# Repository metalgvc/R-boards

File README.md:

#### Eagle libs, boards, schemes

##### mgvc.lbr
EAGLE lib contain following devices:
- GPS module GP4SF1109F2
- KL-5641-ASR LED
- MT3608
- CDRH74NP-220MC-B
- CN3085
- 40TPS12
- MICROSD-MR08
- SG5841

##### GP4SF1109F2-smd-to-dip
SMD to DIP adaptor for GP4SF1109F2 module

##### DC-DC-step-up-MT3608
DC/DC set-up converter board based on MT3608

##### DC-DC-sepic-MT3608
DC/DC SEPIC converter based on MT3608

##### GPS-module-board
GPS module GP4SF1109F2 board with bi-directional logic level converter 1.8 <-> 3.3/5... 
and linear stabilizator to 1.8v

##### Ni-MH-charger
Ni-MH charger module based on CN3085 
(module constructed without temperature monitoring)

##### tl494-pulse-generator
PWM on TL494 with mosfet

##### RF-detector

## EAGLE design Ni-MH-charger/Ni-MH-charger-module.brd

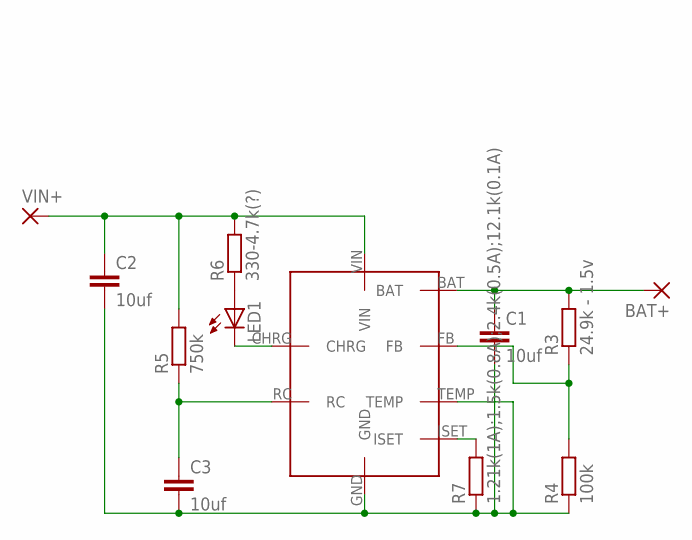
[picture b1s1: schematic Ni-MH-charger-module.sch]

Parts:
BAT+: SMD5; SMD2,54-5,08
C1, C2, C3: 10uf; C0805
LED1: LEDCHIPLED_0805; CHIPLED_0805
R3: 24.9k - 1.5v; R0805
R4: 100k; R0805
R5: 750k; R0805
R6: 330-4.7k(?); R0805
R7: 1.21k(1A);1.5k(0.8A);2.4k(0.5A);12.1k(0.1A); R0805
U$1: CN3085
VIN+: SMD5; SMD2,54-5,08

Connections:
BAT+: BAT+.1, C1.1, R3.2, U$1.BAT
GND: C1.2, C2.2, C3.2, R4.1, R7.1, U$1.GND, U$1.TEMP
unnamed: R3.1, R4.2, U$1.FB
unnamed: R7.2, U$1.ISET
unnamed: C3.1, R5.1, U$1.RC
unnamed: LED1.A, R6.1
unnamed: LED1.C, U$1.CHRG
VIN: C2.1, R5.2, R6.2, U$1.VIN, VIN+.1

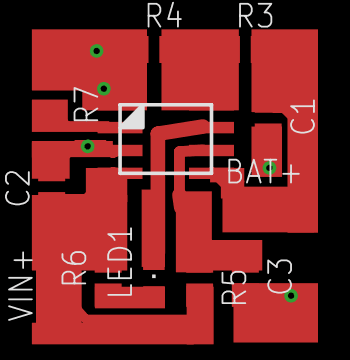
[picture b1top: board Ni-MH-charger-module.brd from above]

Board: 2 copper layers, 12 parts (0 on the bottom side), 8 nets.

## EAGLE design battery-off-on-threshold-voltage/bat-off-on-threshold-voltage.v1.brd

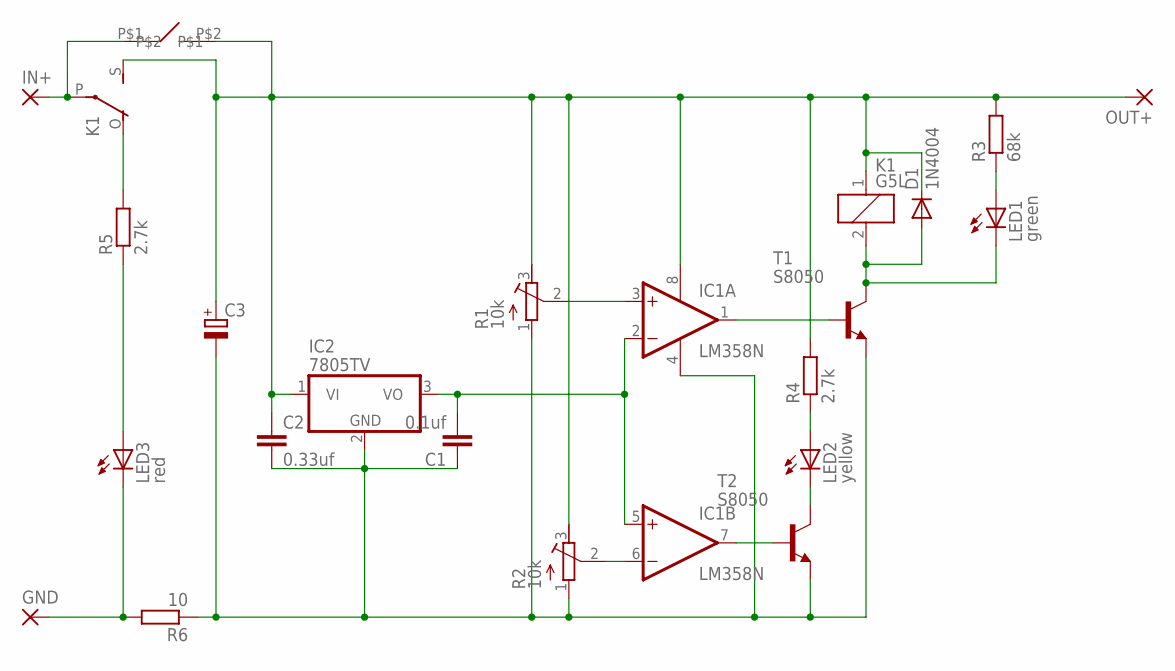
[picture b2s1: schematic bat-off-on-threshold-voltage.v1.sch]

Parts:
C1: 0.1uf; C050-025X075
C2: 0.33uf; C050-025X075
C3: CPOL-EUE2.5-6; E2,5-6
D1: 1N4004; DO41-10
GND: 3,81/1,1
IC1: LM358N; DIL08
IC2: 7805TV; TO220V
IN+: 3,81/1,1
K1: G5L; G5LE
LED1: green; LED3MM
LED2: yellow; LED3MM
LED3: red; LED3MM
OUT+: 3,81/1,1
R1, R2: 10k; RTRIM3296W
R3: 68k; 0204/7
R4, R5: 2.7k; 0204/7
R6: 10; 0204/7
T1, T2: S8050; TO92-EBC
U$1: BTN-6X6

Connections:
GND: C1.1, C2.2, C3.-, IC1.4 (V-), IC2.2 (GND), R1.1 (A), R2.1 (A), R6.1, T1.E, T2.E
unnamed: IC1.1 (OUT), T1.B
unnamed: IC1.7 (OUT), T2.B
unnamed: IC1.3 (+IN), R1.2 (S)
unnamed: IC1.6 (-IN), R2.2 (S)
unnamed: C2.1, C3.+, D1.C, IC1.8 (V+), IC2.1 (VI), K1.1, K1.S, OUT+.1, R1.3 (E), R2.3 (E), R3.2, R4.2, U$1.P$2
unnamed: C1.2, IC1.2 (-IN), IC1.5 (+IN), IC2.3 (VO)
unnamed: LED1.A, R3.1
unnamed: D1.A, K1.2, LED1.K (C), T1.C
unnamed: LED2.K (C), T2.C
unnamed: LED2.A, R4.1
unnamed: IN+.1, K1.P, U$1.P$1
unnamed: LED3.A, R5.1
unnamed: K1.O, R5.2
unnamed: GND.1, LED3.K (C), R6.2

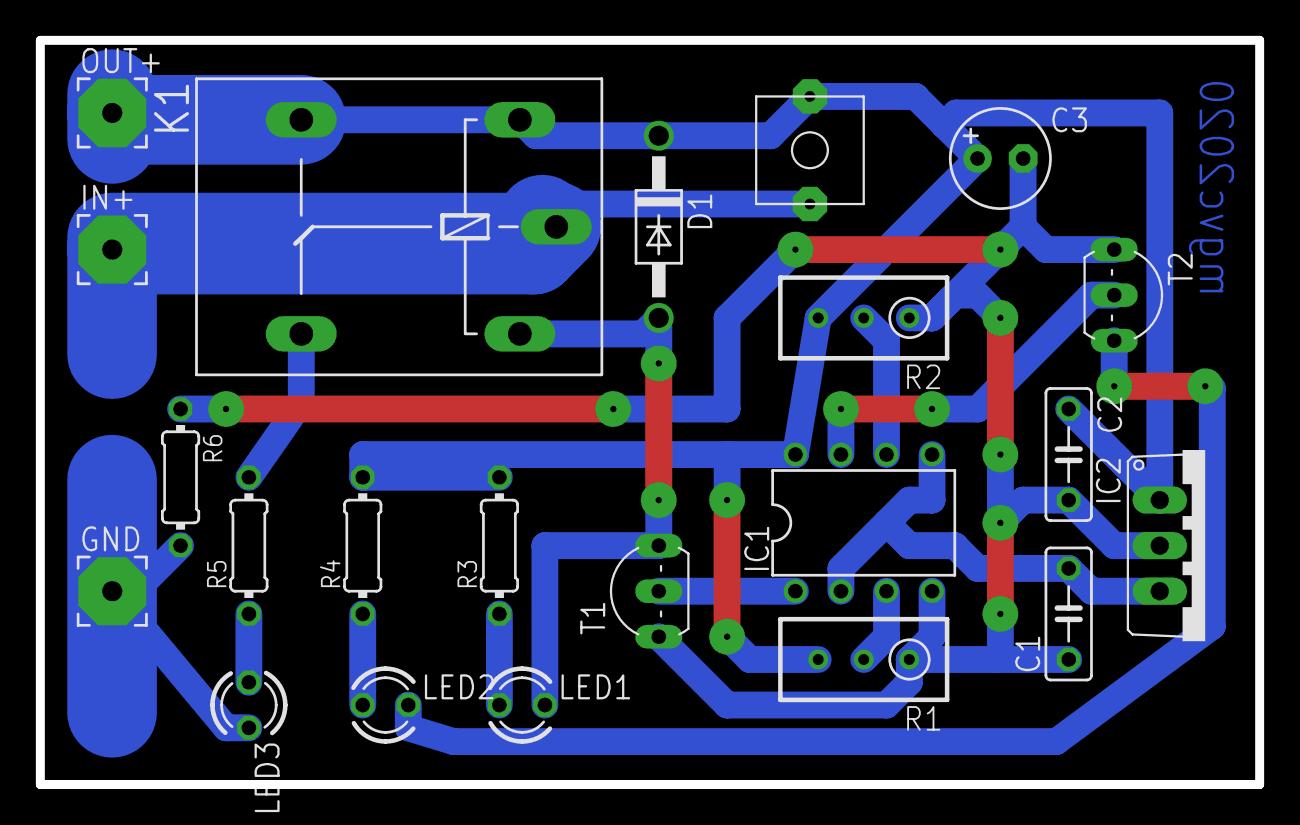
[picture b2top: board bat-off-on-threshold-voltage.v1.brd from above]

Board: 2 copper layers, 68.0 x 41.5 mm, 22 parts (0 on the bottom side), 15 nets.

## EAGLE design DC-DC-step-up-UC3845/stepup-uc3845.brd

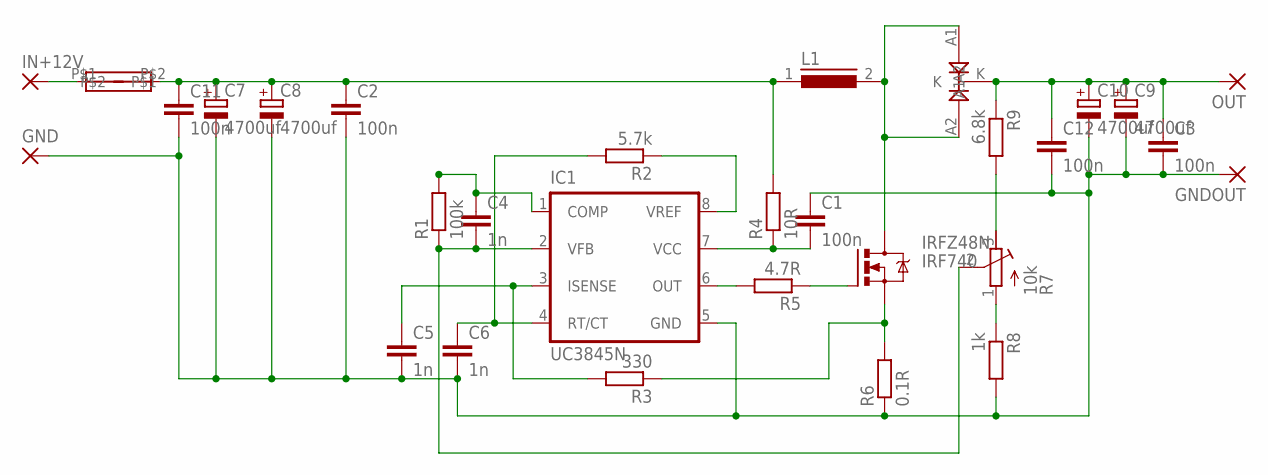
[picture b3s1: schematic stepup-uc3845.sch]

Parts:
C1, C2, C3, C11, C12: 100n; C050-025X075
C4, C5, C6: 1n; C050-025X075
C7, C8: 4700uf; E7,5-16
C9, C10: 4700uf; E7,5-18
F1: 10A; FUSE38X12
GND: 3,81/1,1
GNDOUT: 3,81/1,1
IC1: UC3845N; DIL08
IN+12V: 3,81/1,1
IRFZ48N: IRF740; TO220BV
L1: R3311D11; 11-33
OUT: 3,81/1,1
R1: 100k; 0204/7
R2: 5.7k; 0207/7
R3: 330; 0207/7
R4: 10R; 0617/17
R5: 4.7R; 0207/7
R6: 0.1R; 0922/22
R7: 10k; RTRIM3296W
R8: 1k; 0207/7
R9: 6.8k; 0207/7
U$1: TO-247-SHOTTKY-K; TO-247

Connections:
GND: C1.1, C2.2, C3.2, C5.2, C6.2, C7.-, C8.-, C9.-, C10.-, C11.2, C12.2, GND.1, GNDOUT.1, IC1.5 (GND), R6.1, R8.2
unnamed: C6.1, IC1.4 (RT/CT), R2.2
unnamed: C5.1, IC1.3 (ISENSE), R3.2
unnamed: C4.2, IC1.2 (VFB), R1.1, R7.2 (S)
unnamed: C4.1, IC1.1 (COMP), R1.2
unnamed: IC1.6 (OUT), R5.2
unnamed: IRFZ48N.G, R5.1
unnamed: IC1.8 (VREF), R2.1
unnamed: C1.2, IC1.7 (VCC), R4.1
unnamed: IRFZ48N.S, R3.1, R6.2
unnamed: F1.P$1, IN+12V.1
unnamed: C2.1, C7.+, C8.+, C11.1, F1.P$2, L1.1, R4.2
unnamed: C3.1, C9.+, C10.+, C12.1, OUT.1, R9.1, U$1.K
unnamed: R7.1 (A), R8.1
unnamed: R7.3 (E), R9.2
unnamed: IRFZ48N.D, L1.2, U$1.A1, U$1.A2

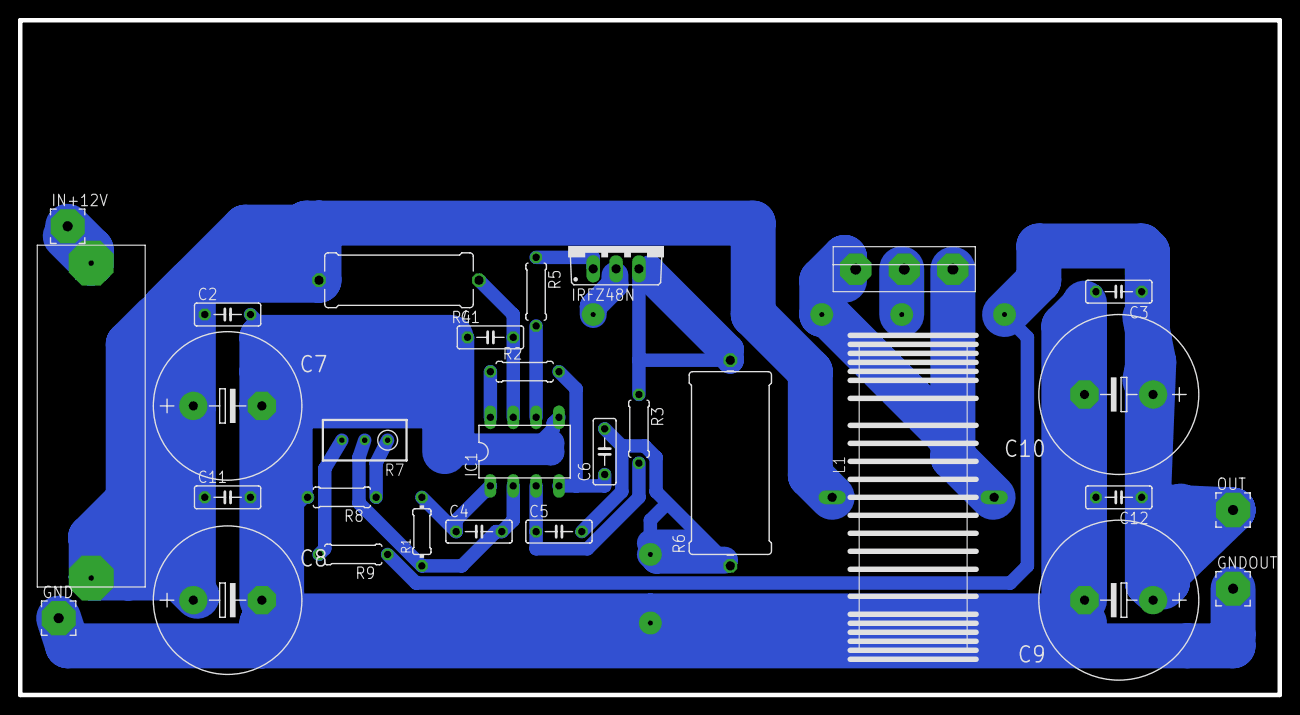
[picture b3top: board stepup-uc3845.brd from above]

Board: 2 copper layers, 140.0 x 75.0 mm, 30 parts (0 on the bottom side), 16 nets.

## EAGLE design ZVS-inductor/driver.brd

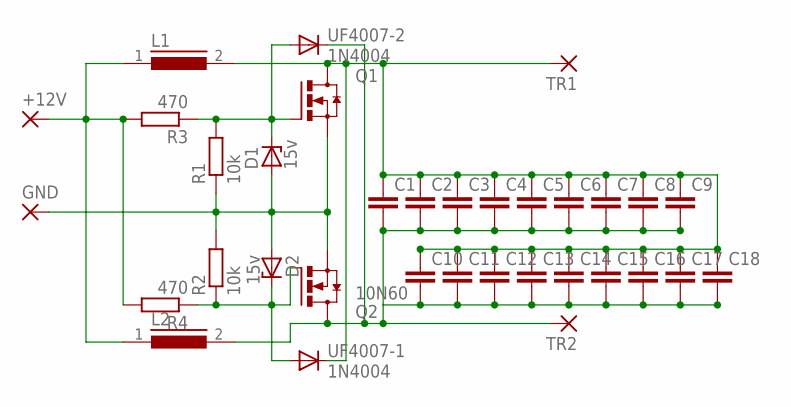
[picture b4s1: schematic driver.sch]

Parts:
+12V: 3,17/1,1
C1, C2, C3, C4, C5, C6, C7, C8, C9, C10, C11, C12, C13, C14, C15, C16, C17, C18: C-EU150-064X183; C150-064X183
D1, D2: 15v; DO35Z10
GND: 3,17/1,1
L1, L2: R2408F11; 11-24
Q1: IRFP250; TO-247AD-V
Q2: 10N60; TO-247AD-V
R1, R2: 10k; 0204/7
R3, R4: 470; 0617/17
TR1, TR2: 3,17/1,1
UF4007-1, UF4007-2: 1N4004; DO41-10

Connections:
unnamed: D1.A, D2.A, GND.1, Q1.S, Q2.S, R1.1, R2.2
unnamed: D1.C, Q1.G, R1.2, R3.1, UF4007-2.A
unnamed: +12V.1, L1.1, L2.1, R3.2, R4.2
unnamed: D2.C, Q2.G, R2.1, R4.1, UF4007-1.A
unnamed: C1.2, C2.2, C3.2, C4.2, C5.2, C6.2, C7.2, C8.2, C9.2, C10.2, C11.2, C12.2, C13.2, C14.2, C15.2, C16.2, C17.2, C18.2, L2.2, Q2.D, TR2.1, UF4007-2.C
unnamed: C1.1, C2.1, C3.1, C4.1, C5.1, C6.1, C7.1, C8.1, C9.1, C10.1, C11.1, C12.1, C13.1, C14.1, C15.1, C16.1, C17.1, C18.1, L1.2, Q1.D, TR1.1, UF4007-1.C

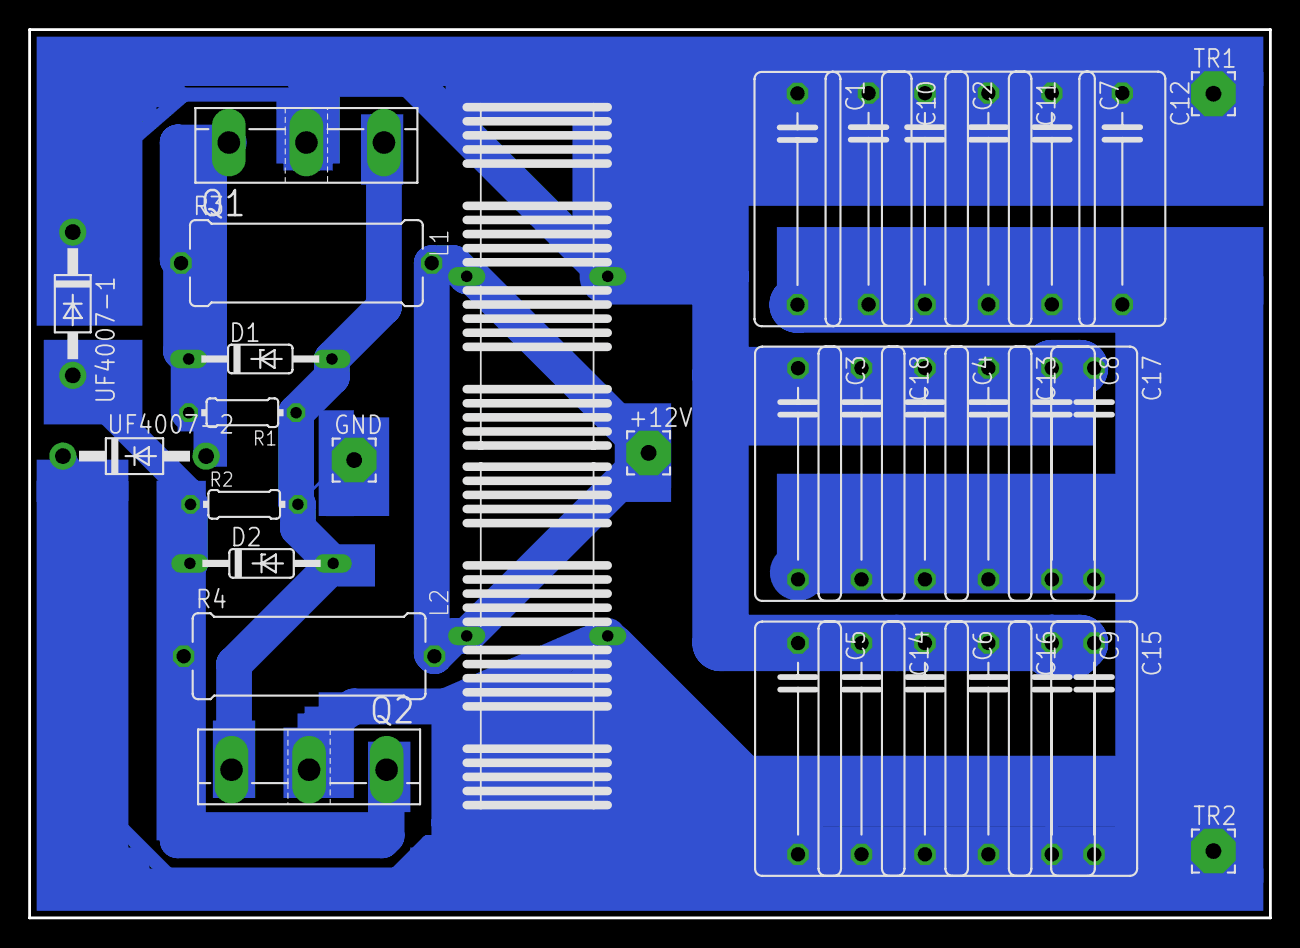
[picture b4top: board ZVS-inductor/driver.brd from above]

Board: 2 copper layers, 88.0 x 63.0 mm, 34 parts (0 on the bottom side), 6 nets.

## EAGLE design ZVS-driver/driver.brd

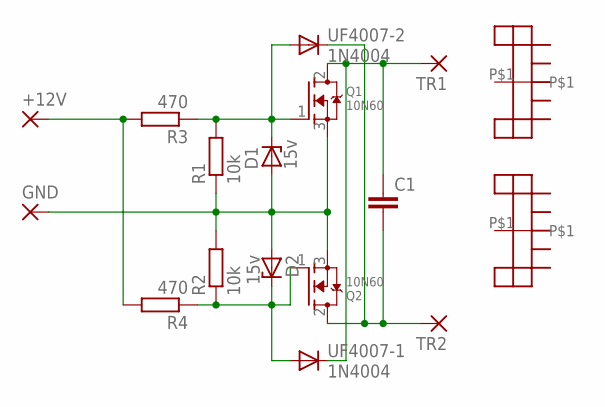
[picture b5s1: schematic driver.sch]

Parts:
+12V: 3,17/1,1
C1: C-EU150-064X183; C150-064X183
D1, D2: 15v; DO35Z10
GND: 3,17/1,1
Q1, Q2: 10N60; TO220V
R1, R2: 10k; 0204/7
R3, R4: 470; 0617/17
TR1, TR2: 3,17/1,1
U$1, U$2: RADIATOR; RAD15X11
UF4007-1, UF4007-2: 1N4004; DO41-10

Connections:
unnamed: D1.A, D2.A, GND.1, Q1.3 (S), Q2.3 (S), R1.1, R2.2
unnamed: D1.C, Q1.1 (G), R1.2, R3.1, UF4007-2.A
unnamed: +12V.1, R3.2, R4.2
unnamed: D2.C, Q2.1 (G), R2.1, R4.1, UF4007-1.A
unnamed: C1.1, Q1.2 (D), TR1.1, UF4007-1.C
unnamed: C1.2, Q2.2 (D), TR2.1, UF4007-2.C

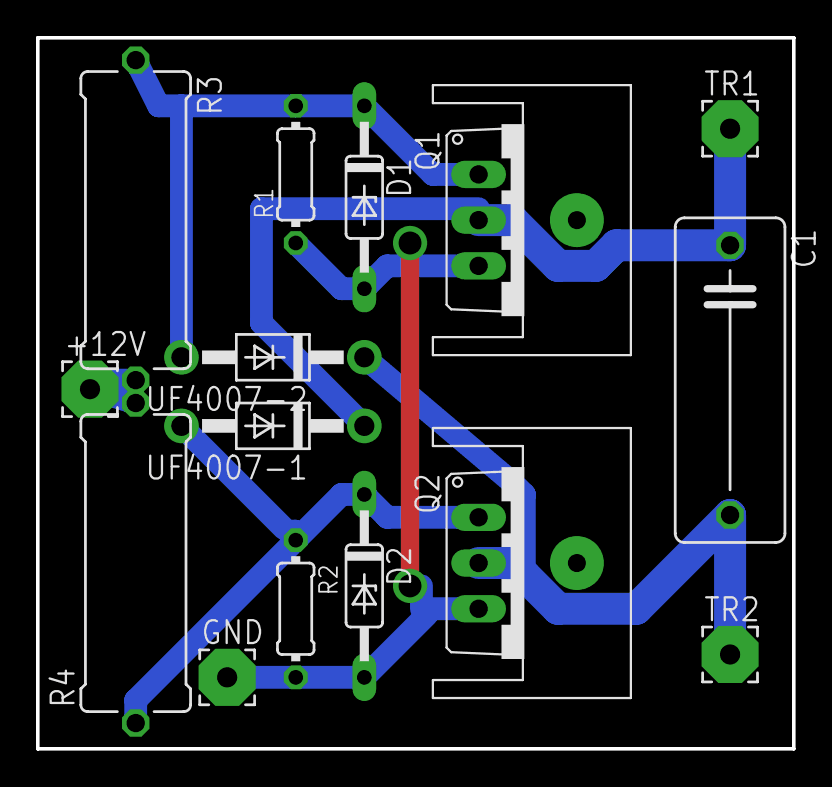
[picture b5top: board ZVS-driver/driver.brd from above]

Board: 2 copper layers, 42.0 x 39.5 mm, 17 parts (0 on the bottom side), 6 nets.

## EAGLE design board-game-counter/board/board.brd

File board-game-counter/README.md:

card board games counter on ATTiny13

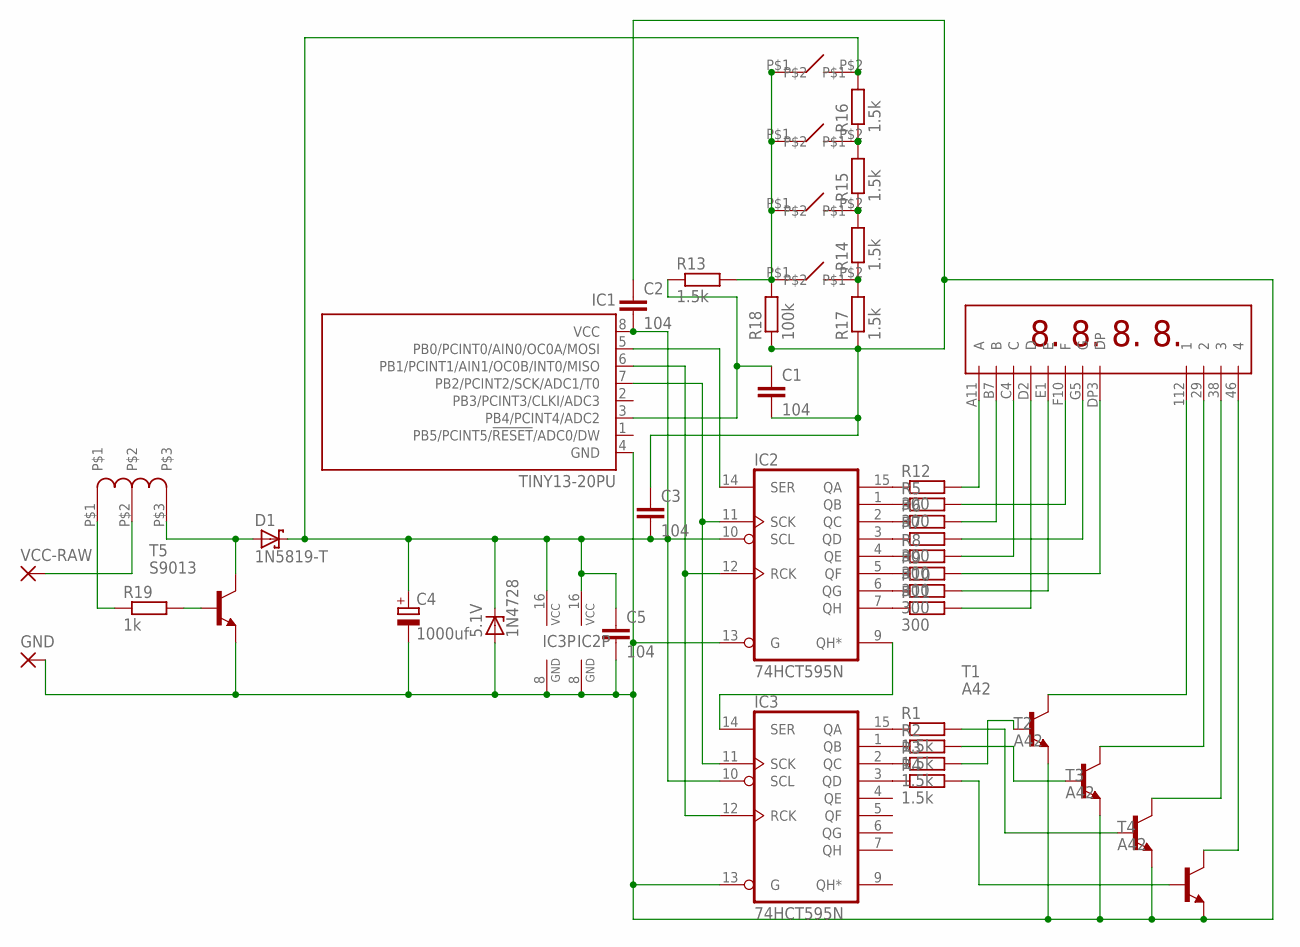
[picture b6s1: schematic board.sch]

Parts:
5.1V: 1N4728; DO41Z10
BTN1, BTN2, BTN3, BTN4: BTN-6X6
C1, C2, C3, C5: 104; C050-025X075
C4: 1000uf; E3,5-8
D1: 1N5819-T; DO41-7.6
GND: 2,54/0,8
IC1: TINY13-20PU; DIL08
IC2, IC3: 74HCT595N; DIL16
R1, R2, R3, R4: 1.5k; 0207/2V
R5, R7, R8, R9, R10, R11, R12: 300; 0207/2V
R6: R-EU_0207/2V; 0207/2V
R13, R14, R15, R16, R17: 1.5k; 0204/7
R18: 100k; 0204/7
R19: 1k; 0207/2V
T1, T2, T3, T4: A42; TO92-EBC
T5: S9013; TO92-EBC
U$1: KL-5641-ASR
U$3: TRANS
VCC-RAW: 2,54/0,8

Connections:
GND: 5.1V.A, C1.2, C2.1, C3.1, C4.-, C5.2, GND.1, IC1.4 (GND), IC2.8 (GND), IC2.13 (G), IC3.8 (GND), IC3.13 (G), R17.1, R18.1, T1.E, T2.E, T3.E, T4.E, T5.E
unnamed: R10.2, U$1.E1 (E)
unnamed: R11.2, U$1.D2 (D)
unnamed: R9.2, U$1.DP3 (DP)
unnamed: R8.2, U$1.C4 (C)
unnamed: R7.2, U$1.G5 (G)
unnamed: R6.2, U$1.B7 (B)
unnamed: R5.2, U$1.F10 (F)
unnamed: R12.2, U$1.A11 (A)
unnamed: IC2.9 (QH*), IC3.14 (SER)
unnamed: IC3.15 (QA), R1.1
unnamed: R1.2, T3.B
unnamed: R2.2, T2.B
unnamed: R4.2, T4.B
unnamed: T1.C, U$1.112 (1)
unnamed: T2.C, U$1.29 (2)
unnamed: T3.C, U$1.38 (3)
unnamed: T4.C, U$1.46 (4)
unnamed: IC1.5 (PB0/PCINT0/AIN0/OC0A/MOSI), IC2.14 (SER)
unnamed: D1.A, T5.C, U$3.P$3
unnamed: IC3.1 (QB), R2.1
unnamed: IC3.2 (QC), R3.1
unnamed: IC3.3 (QD), R4.1
unnamed: R3.2, T1.B
unnamed: IC2.7 (QH), R11.1
unnamed: IC2.6 (QG), R10.1
unnamed: IC2.5 (QF), R9.1
unnamed: IC2.4 (QE), R8.1
unnamed: IC2.3 (QD), R7.1
unnamed: IC2.2 (QC), R6.1
unnamed: IC2.1 (QB), R5.1
unnamed: IC2.15 (QA), R12.1
unnamed: C1.1, IC1.3 (PB4/PCINT4/ADC2), R13.1
unnamed: BTN1.P$1, BTN2.P$1, BTN3.P$1, BTN4.P$1, R13.2, R18.2
unnamed: BTN4.P$2, R14.1, R17.2
unnamed: BTN3.P$2, R14.2, R15.1
unnamed: BTN2.P$2, R15.2, R16.1
unnamed: R19.2, T5.B
unnamed: R19.1, U$3.P$1
RCK: IC1.6 (PB1/PCINT1/AIN1/OC0B/INT0/MISO), IC2.12 (RCK), IC3.12 (RCK)
SCK: IC1.7 (PB2/PCINT2/SCK/ADC1/T0), IC2.11 (SCK), IC3.11 (SCK)
VCC: 5.1V.C, BTN1.P$2, C2.2, C3.2, C4.+, C5.1, D1.C, IC1.8 (VCC), IC2.10 (SCL), IC2.16 (VCC), IC3.10 (SCL), IC3.16 (VCC), R16.2
VCC-RAW: U$3.P$2, VCC-RAW.1

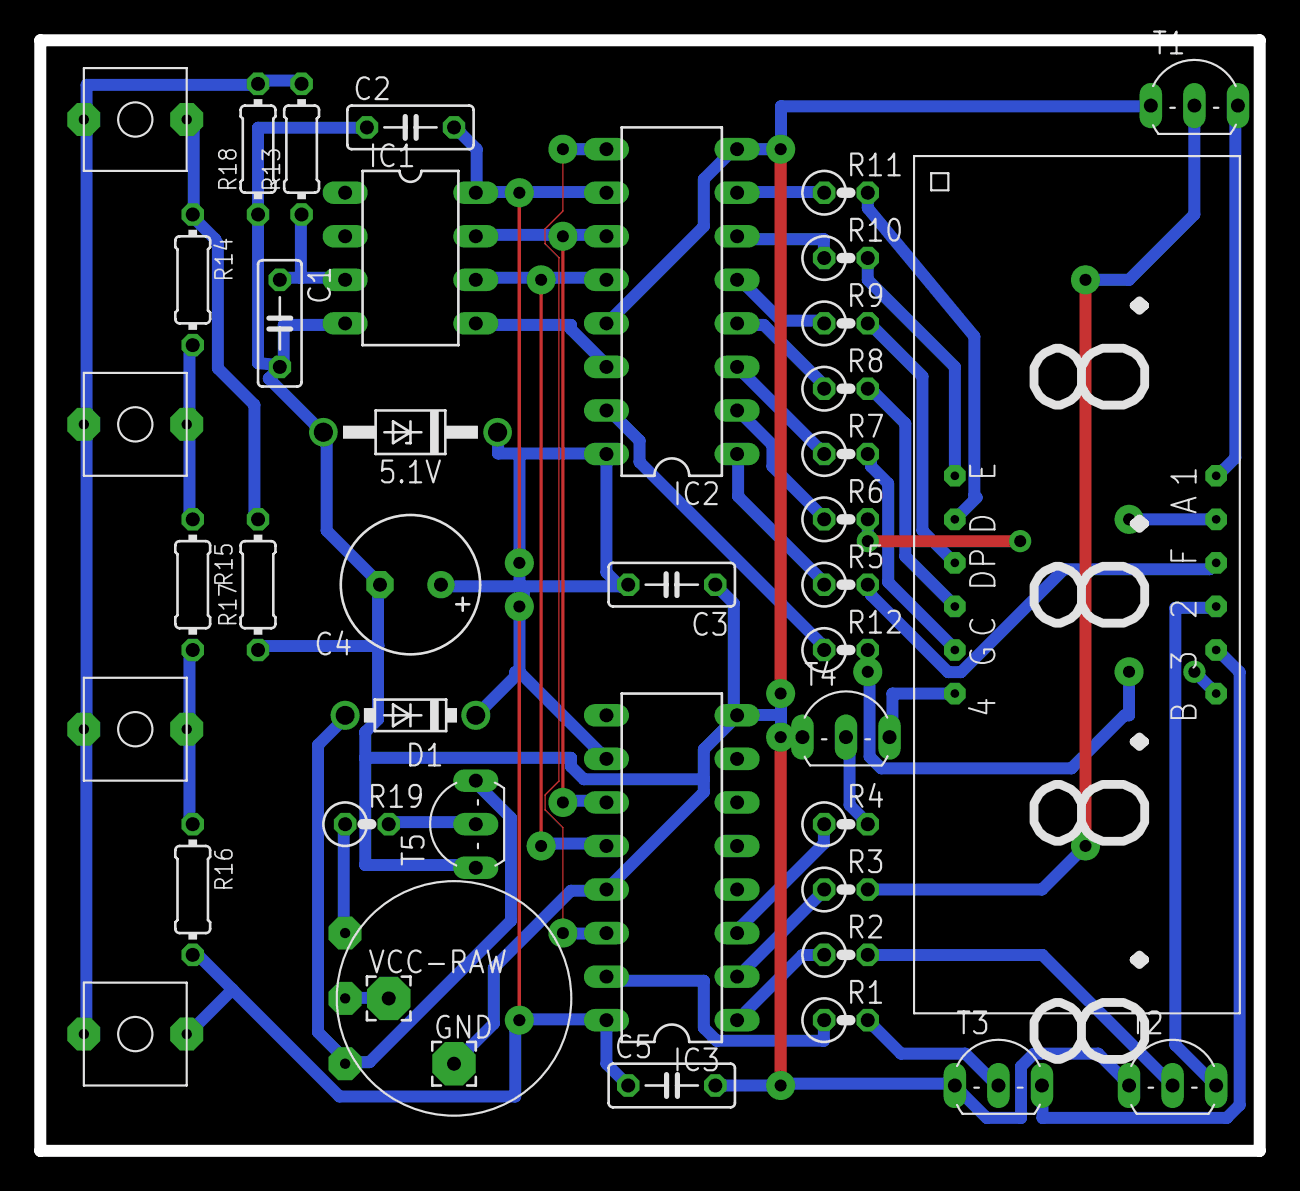
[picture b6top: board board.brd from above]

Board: 2 copper layers, 71.1 x 64.8 mm, 42 parts (0 on the bottom side), 43 nets.

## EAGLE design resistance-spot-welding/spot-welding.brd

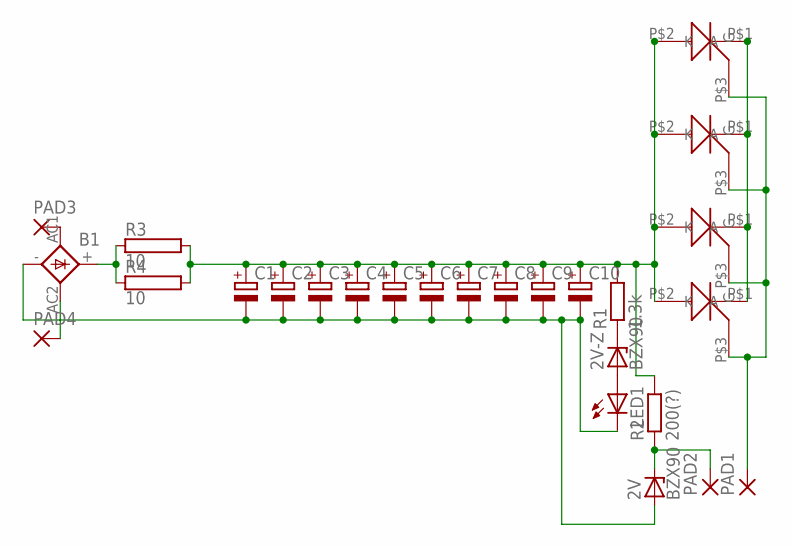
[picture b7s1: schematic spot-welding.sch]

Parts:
2V, 2V-Z: BZX90; DO34Z7
B1: KBU
C1, C2, C3, C4, C5, C6, C7, C8, C9, C10: CPOL-EUE10-30; EB30D
LED1: LED3MM
PAD1, PAD2, PAD3, PAD4: 3,17/1,1
R1: 1.3k; 0204/7
R2: 200(?); 0204/7
R3, R4: 10; KH214R-8
U$1, U$2, U$3, U$4: 40TPS12

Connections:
unnamed: 2V.A, B1.-, C1.-, C2.-, C3.-, C4.-, C5.-, C6.-, C7.-, C8.-, C9.-, C10.-, LED1.K (C)
unnamed: 2V-Z.C, R1.1
unnamed: PAD1.1, U$1.P$3 (G), U$2.P$3 (G), U$3.P$3 (G), U$4.P$3 (G)
unnamed: U$1.P$1 (K), U$2.P$1 (K), U$3.P$1 (K), U$4.P$1 (K)
unnamed: 2V-Z.A, LED1.A
unnamed: 2V.C, PAD2.1, R2.1
unnamed: C1.+, C2.+, C3.+, C4.+, C5.+, C6.+, C7.+, C8.+, C9.+, C10.+, R1.2, R2.2, R3.2, R4.2, U$1.P$2 (A), U$2.P$2 (A), U$3.P$2 (A), U$4.P$2 (A)
unnamed: B1.+, R3.1, R4.1
unnamed: B1.AC1, PAD3.1
unnamed: B1.AC2, PAD4.1

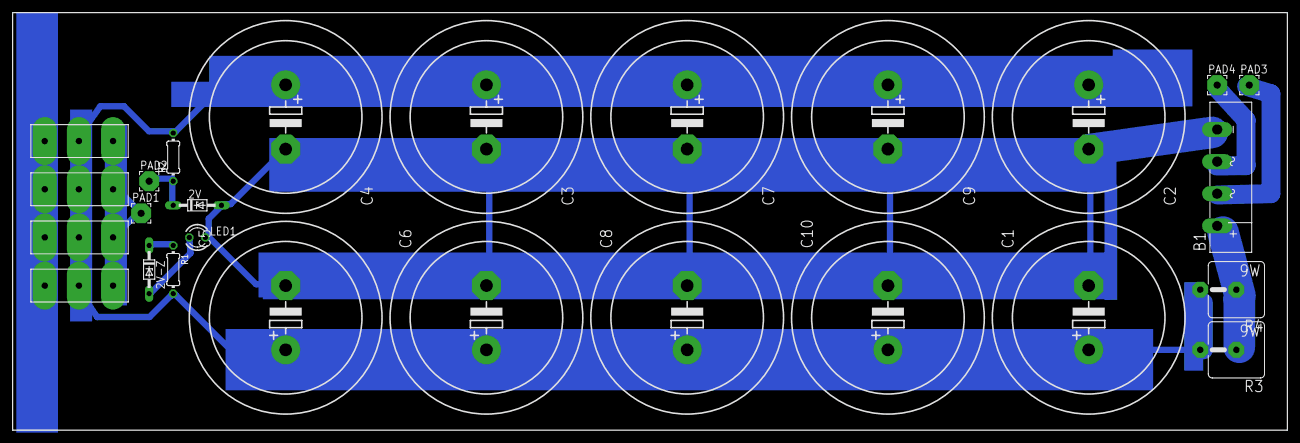
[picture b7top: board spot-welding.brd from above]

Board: 2 copper layers, 201.6 x 66.0 mm, 26 parts (0 on the bottom side), 10 nets.

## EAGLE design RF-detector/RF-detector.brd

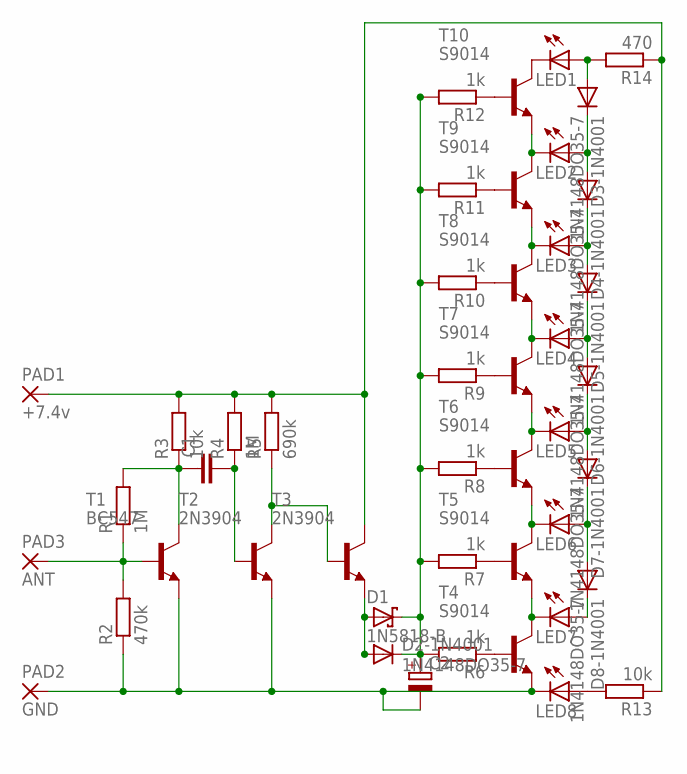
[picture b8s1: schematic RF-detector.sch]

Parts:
C1: C-EU050-024X044; C050-024X044
C2: CPOL-EUE1.8-4; E1,8-4
D1: 1N5818-B; DO41-7.6
D2-1N4001, D3-1N4001, D4-1N4001, D5-1N4001, D6-1N4001, D7-1N4001, D8-1N4001: 1N4148DO35-7; DO35-7
LED1, LED2, LED3, LED4, LED5, LED6, LED7, LED8: LED3MM
PAD1: +7.4v; 2,54/0,8
PAD2: GND; 2,54/0,8
PAD3: ANT; 2,54/0,8
R1, R4: 1M; 0204/7
R2: 470k; 0204/7
R3, R13: 10k; 0204/7
R5: 690k; 0204/7
R6, R7, R8, R9, R10, R11, R12: 1k; 0204/7
R14: 470; 0204/7
T1: BC547; TO92
T2, T3: 2N3904; TO92
T4, T5, T6, T7, T8, T9, T10: S9014; TO92-EBC

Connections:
unnamed: PAD3.1, R1.1, R2.2, T1.2 (B)
unnamed: C1.1, R1.2, R3.1, T1.3 (C)
unnamed: C1.2, R4.1, T2.2 (B)
unnamed: R5.1, T2.1 (C), T3.2 (B)
unnamed: PAD1.1, R3.2, R4.2, R5.2, R13.1, R14.1, T3.1 (C)
unnamed: C2.-, LED8.K (C), PAD2.1, R2.1, T1.1 (E), T2.3 (E), T4.E
unnamed: D1.A, D2-1N4001.A, T3.3 (E)
unnamed: R6.1, T4.B
unnamed: C2.+, D1.C, D2-1N4001.C, R6.2, R7.2, R8.2, R9.2, R10.2, R11.2, R12.2
unnamed: R7.1, T5.B
unnamed: R8.1, T6.B
unnamed: R9.1, T7.B
unnamed: R10.1, T8.B
unnamed: R11.1, T9.B
unnamed: R12.1, T10.B
unnamed: LED2.K (C), T9.C, T10.E
unnamed: LED3.K (C), T8.C, T9.E
unnamed: LED4.K (C), T7.C, T8.E
unnamed: LED5.K (C), T6.C, T7.E
unnamed: LED6.K (C), T5.C, T6.E
unnamed: LED7.K (C), T4.C, T5.E
unnamed: LED1.K (C), T10.C
unnamed: D3-1N4001.A, LED1.A, R14.2
unnamed: D3-1N4001.C, D4-1N4001.A, LED2.A
unnamed: D4-1N4001.C, D5-1N4001.A, LED3.A
unnamed: D5-1N4001.C, D6-1N4001.A, LED4.A
unnamed: D6-1N4001.C, D7-1N4001.A, LED5.A
unnamed: D7-1N4001.C, D8-1N4001.A, LED6.A
unnamed: D8-1N4001.C, LED7.A
unnamed: LED8.A, R13.2

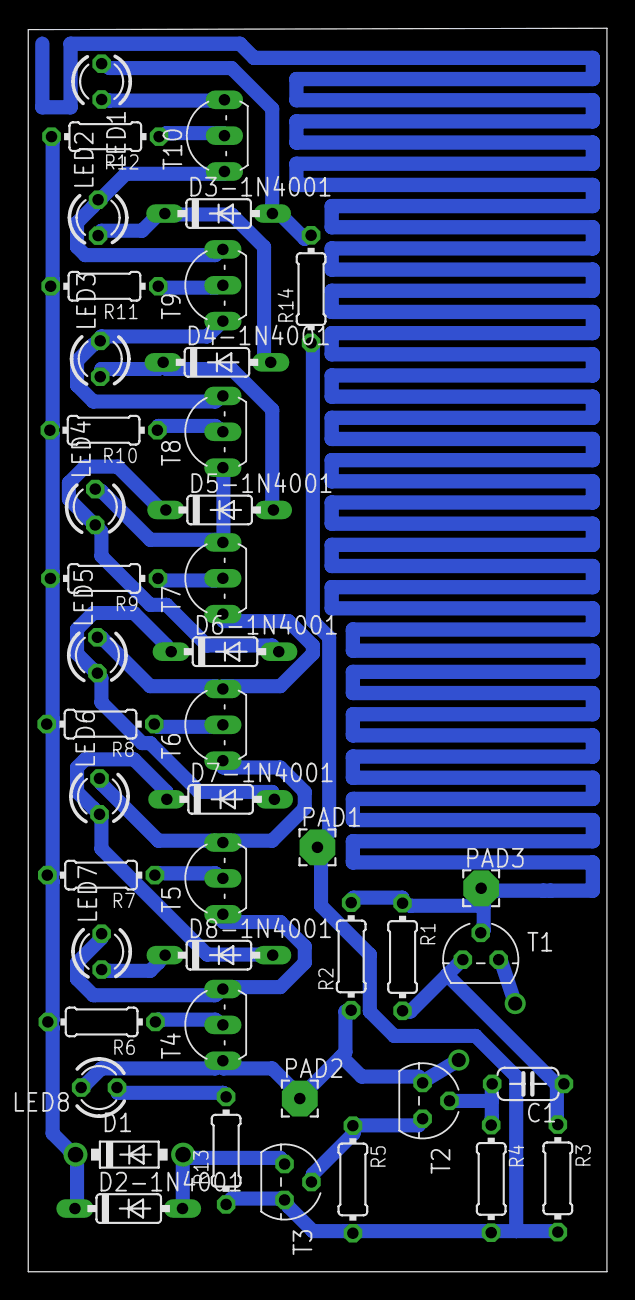
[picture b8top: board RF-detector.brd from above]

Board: 2 copper layers, 41.0 x 88.1 mm, 44 parts (0 on the bottom side), 30 nets.

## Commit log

2019-03-17 mgvc.lbr & GP4SF1109F2-smd-to-dip
2019-03-17 fix mgvc.lbr
2019-03-17 updated mgvc.lbr -> GP4SF1109F2
2019-03-17 GP4SF1109F2-smd-to-dip updated
2019-03-18 removed GP4SF1109F2-smd-to-dip/GP4SF1109F2.pro
2019-03-24 updated mgvc.lbr & added DC-DC-step-up-MT3608 and GPS-module boards
2019-03-29 DC-DC boards updated
2020-01-03 Ni-MH-charger-module
2020-01-03 mgvc.lbr - CN3085 added
2020-01-30 Ni-MH-charger updated
2020-01-30 updated mgvc.lbr
2020-01-30 tl494-pulse-generator
2020-01-30 RF-detector
2020-02-21 AA-BAT-SOCKET added & updated LED 7-segment indicator
2020-02-21 AA-BAT-SOCKET updated
2020-03-07 board-game-counter
2020-04-11 mgvc.lbr RADIATOR 11x15 added
2020-04-11 resistance-spot-welding added
2020-04-11 ZVS-driver added
2020-04-11 board-game-counter updated
2020-04-12 ZVS-driver updated
2020-04-19 ZVS-inductor
2020-05-25 DC-DC-step-up-UC3845
2020-05-27 battery-off-on-threshold-voltage
2020-05-31 Ni-MH-charger updates
